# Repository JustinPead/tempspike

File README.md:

Tempspike PCB Design Files

The Tempspike board was designed to be a conductivity sensor for multiple pads in the event that some of them fail due to corrosion or seperation.

Please contact me if you are not comfortable with making this board for your work.

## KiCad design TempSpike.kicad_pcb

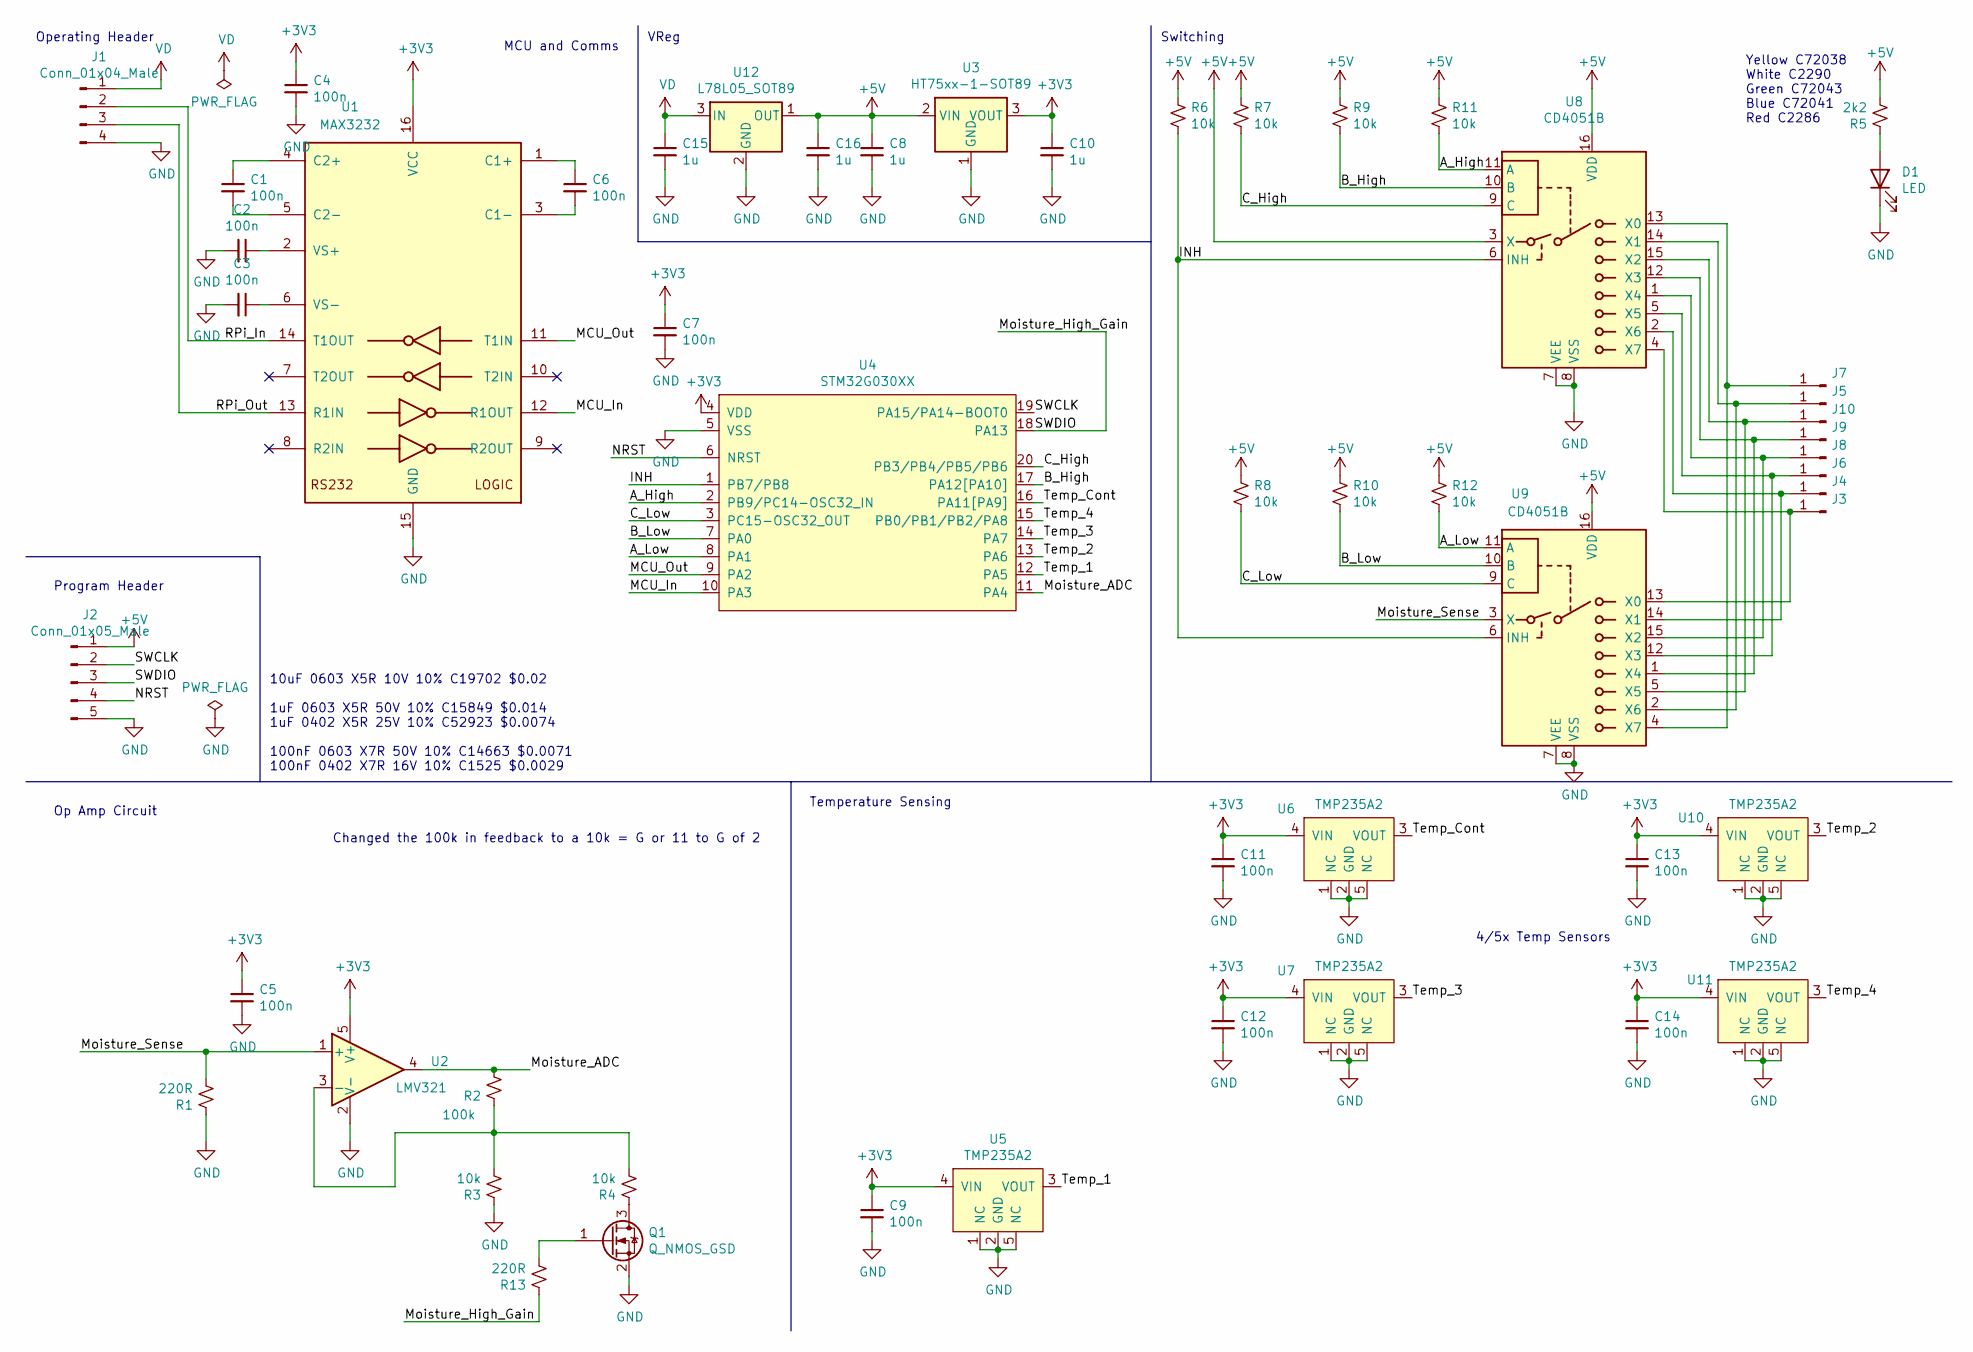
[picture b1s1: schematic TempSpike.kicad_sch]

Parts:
C1, C2, C3, C4, C5, C6, C7, C9, C11, C12, C13, C14: 100n; C_0402_1005Metric; LCSC C1525
C8, C10, C15, C16: 1u; C_0402_1005Metric; LCSC C52923
D1: LED; D_0603_1608Metric; LCSC C72043
J1: Conn_01x04_Male; PinHeader_1x04_P2.54mm_Vertical; LCSC 0
J2: Conn_01x05_Male; PinHeader_1x05_P2.54mm_Vertical; LCSC 0
J3, J4, J5, J6, J7, J8, J9, J10: Conn_01x01_Male; TestPoint_Pad_2.0x2.0mm; LCSC 0
Q1: Q_NMOS_GSD; SOT-23; LCSC C8545
R1: 220R; R_0805_2012Metric; LCSC C17557
R2: 100k; R_0805_2012Metric; LCSC C149504
R3: 10k; R_0805_2012Metric; LCSC C17414
R4, R6, R7, R8, R9, R10, R11, R12: 10k; R_0402_1005Metric; LCSC C25744
R5: 2k2; R_0402_1005Metric; LCSC C25879
R13: 220R; R_0402_1005Metric; LCSC C25091
U1: MAX3232; SOIC-16_3.9x9.9mm_P1.27mm; LCSC C7258
U2: LMV321; SOT-23-5; LCSC C7972
U3: HT75xx-1-SOT89; SOT-89-3; LCSC C14289
U4: STM32G030XX; TSSOP-20_4.4x6.5mm_P0.65mm; LCSC C724040
U5, U6, U7, U10, U11: TMP235A2; SOT-353_SC-70-5; LCSC C2868485
U8, U9: CD4051B; SOIC-16_3.9x9.9mm_P1.27mm; LCSC C21379
U12: L78L05_SOT89; SOT-89-3; LCSC C71136

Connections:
+3V3: C4.1, C5.1, C7.1, C9.1, C10.1, C11.1, C12.1, C13.1, C14.1, U1.16 (VCC), U2.5 (V+), U3.3 (VOUT), U4.4 (VDD), U5.4 (VIN), U6.4 (VIN), U7.4 (VIN), U10.4 (VIN), U11.4 (VIN)
+5V: C8.1, C16.1, J2.1, R5.2, R6.1, R7.1, R8.1, R9.1, R10.1, R11.1, R12.1, U3.2 (VIN), U8.3 (X), U8.16 (VDD), U9.16 (VDD), U12.1 (OUT)
/A_High: R11.2, U4.2 (PB9/PC14-OSC32_IN), U8.11 (A)
/A_Low: R12.2, U4.8 (PA1), U9.11 (A)
/B_High: R9.2, U4.17 (PA12[PA10]), U8.10 (B)
/B_Low: R10.2, U4.7 (PA0), U9.10 (B)
/C_High: R7.2, U4.20 (PB3/PB4/PB5/PB6), U8.9 (C)
/C_Low: R8.2, U4.3 (PC15-OSC32_OUT), U9.9 (C)
/INH: R6.2, U4.1 (PB7/PB8), U8.6 (INH), U9.6 (INH)
/MCU_In: U1.12 (R1OUT), U4.10 (PA3)
/MCU_Out: U1.11 (T1IN), U4.9 (PA2)
/Moisture_ADC: R2.2, U2.4, U4.11 (PA4)
/Moisture_High_Gain: J2.3, R13.1, U4.18 (PA13)
/Moisture_Sense: R1.2, U2.1 (+), U9.3 (X)
/NRST: J2.4, U4.6 (NRST)
/RPi_In: J1.2, U1.14 (T1OUT)
/RPi_Out: J1.3, U1.13 (R1IN)
/SWCLK: J2.2, U4.19 (PA15/PA14-BOOT0)
/Temp_1: U4.12 (PA5), U5.3 (VOUT)
/Temp_2: U4.13 (PA6), U10.3 (VOUT)
/Temp_3: U4.14 (PA7), U7.3 (VOUT)
/Temp_4: U4.15 (PB0/PB1/PB2/PA8), U11.3 (VOUT)
/Temp_Cont: U4.16 (PA11[PA9]), U6.3 (VOUT)
GND: C2.2, C3.2, C4.2, C5.2, C7.2, C8.2, C9.2, C10.2, C11.2, C12.2, C13.2, C14.2, C15.2, C16.2, D1.1 (K), J1.4, J2.5, Q1.2 (S), R1.1, R3.1, U1.15 (GND), U2.2 (V-), U3.1 (GND), U4.5 (VSS), U5.1 (NC), U5.2 (GND), U5.5 (NC), U6.1 (NC), U6.2 (GND), U6.5 (NC), U7.1 (NC), U7.2 (GND), U7.5 (NC), U8.7 (VEE), U8.8 (VSS), U9.7 (VEE), U9.8 (VSS), U10.1 (NC), U10.2 (GND), U10.5 (NC), U11.1 (NC), U11.2 (GND), U11.5 (NC), U12.2 (GND)
unnamed: C1.1, U1.4 (C2+)
unnamed: C1.2, U1.5 (C2-)
unnamed: C2.1, U1.2 (VS+)
unnamed: C3.1, U1.6 (VS-)
unnamed: C6.1, U1.1 (C1+)
unnamed: C6.2, U1.3 (C1-)
unnamed: D1.2 (A), R5.1
unnamed: J3.1, U8.4 (X7), U9.13 (X0)
unnamed: J4.1, U8.2 (X6), U9.14 (X1)
unnamed: J5.1, U8.14 (X1), U9.2 (X6)
unnamed: J6.1, U8.5 (X5), U9.12 (X3)
unnamed: J7.1, U8.13 (X0), U9.4 (X7)
unnamed: J8.1, U8.1 (X4), U9.15 (X2)
unnamed: J9.1, U8.12 (X3), U9.1 (X4)
unnamed: J10.1, U8.15 (X2), U9.5 (X5)
unnamed: Q1.1 (G), R13.2
unnamed: Q1.3 (D), R4.1
unnamed: R2.1, R3.2, R4.2, U2.3 (-)
VD: C15.1, J1.1, U12.3 (IN)

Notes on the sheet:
4/5x Temp Sensors
Switching
10uF 0603 X5R 10V 10% C19702 $0.02 1uF 0603 X5R 50V 10% C15849 $0.014 1uF 0402 X5R 25V 10% C52923 $0.0074 100nF 0603 X7R 50V 10% C14663 $0.0071 100nF 0402 X7R 16V 10% C1525 $0.0029
Operating Header
Program Header
Changed the 100k in feedback to a 10k = G or 11 to G of 2
Yellow C72038 White C2290 Green C72043 Blue C72041 Red C2286
Op Amp Circuit
Temperature Sensing
VReg
MCU and Comms

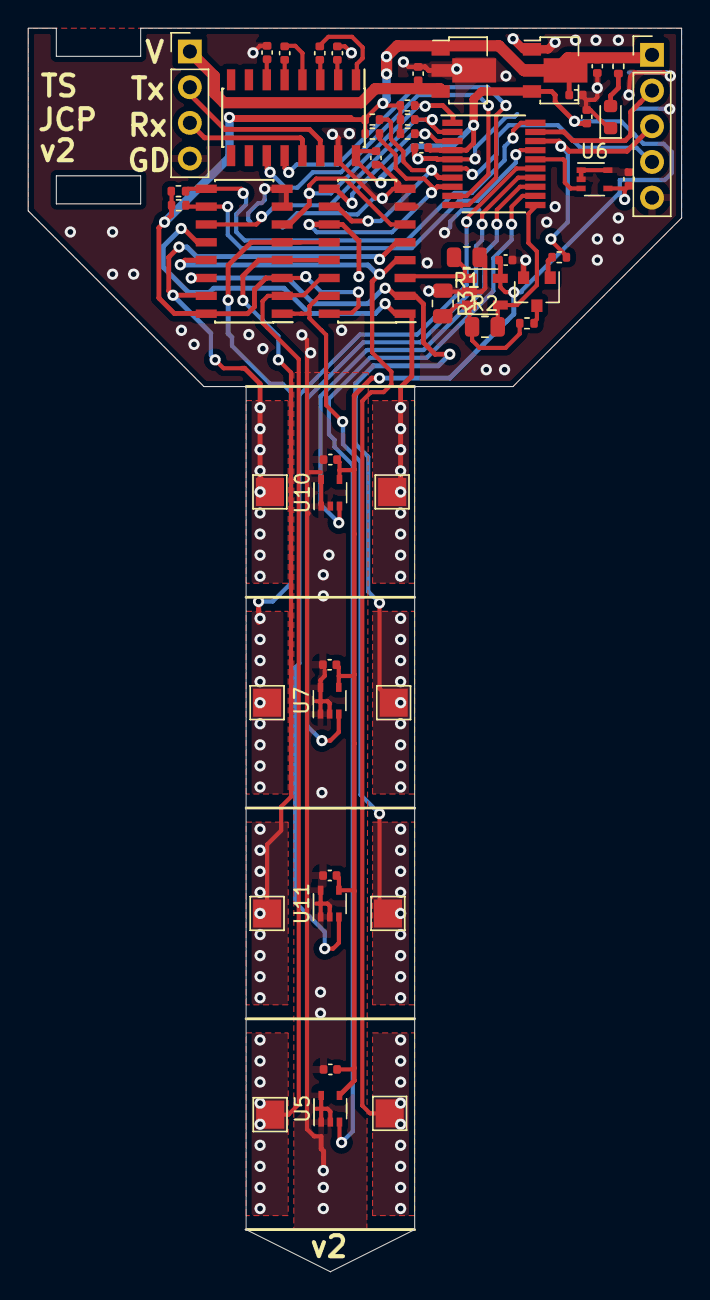
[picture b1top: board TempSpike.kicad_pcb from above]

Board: 2 copper layers, 46.5 x 88.5 mm, 53 parts (0 on the bottom side), 43 nets.

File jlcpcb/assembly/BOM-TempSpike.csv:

Comment,Designator,Footprint,LCSC
Conn_01x04_Male,"J1,J2",PinHeader_1x04_P2.54mm_Vertical,0
HT75xx-1-SOT89,U3,SOT-89-3,C14289
100k,R2,R_0805_2012Metric,C149504
100n,"C1,C11,C12,C13,C14,C2,C3,C4,C5,C6,C7,C9",C_0402_1005Metric,C1525
10k,R3,R_0805_2012Metric,C17414
220R,R1,R_0805_2012Metric,C17557
CD4051B,"U8,U9",SOIC-16_3.9x9.9mm_P1.27mm,C21379
220R,R13,R_0402_1005Metric,C25091
10k,"R10,R11,R12,R4,R6,R7,R8,R9",R_0402_1005Metric,C25744
2k2,R5,R_0402_1005Metric,C25879
TMP235A2,"U10,U11,U5,U6,U7",SOT-353_SC-70-5,C2868485
1u,"C10,C15,C16,C8",C_0402_1005Metric,C52923
STM32G030XX,U4,TSSOP-20_4.4x6.5mm_P0.65mm,C529330
L78L05_SOT89,U12,SOT-89-3,C71136
LED,D1,D_0603_1608Metric,C72043
MAX3232,U1,SOIC-16_3.9x9.9mm_P1.27mm,C7258
LMV321,U2,SOT-23-5,C7972
Q_NMOS_GSD,Q1,SOT-23,C8545
Conn_01x01_Male,"J10,J3,J4,J5,J6,J7,J8,J9",TestPoint_Pad_2.0x2.0mm,DNP
